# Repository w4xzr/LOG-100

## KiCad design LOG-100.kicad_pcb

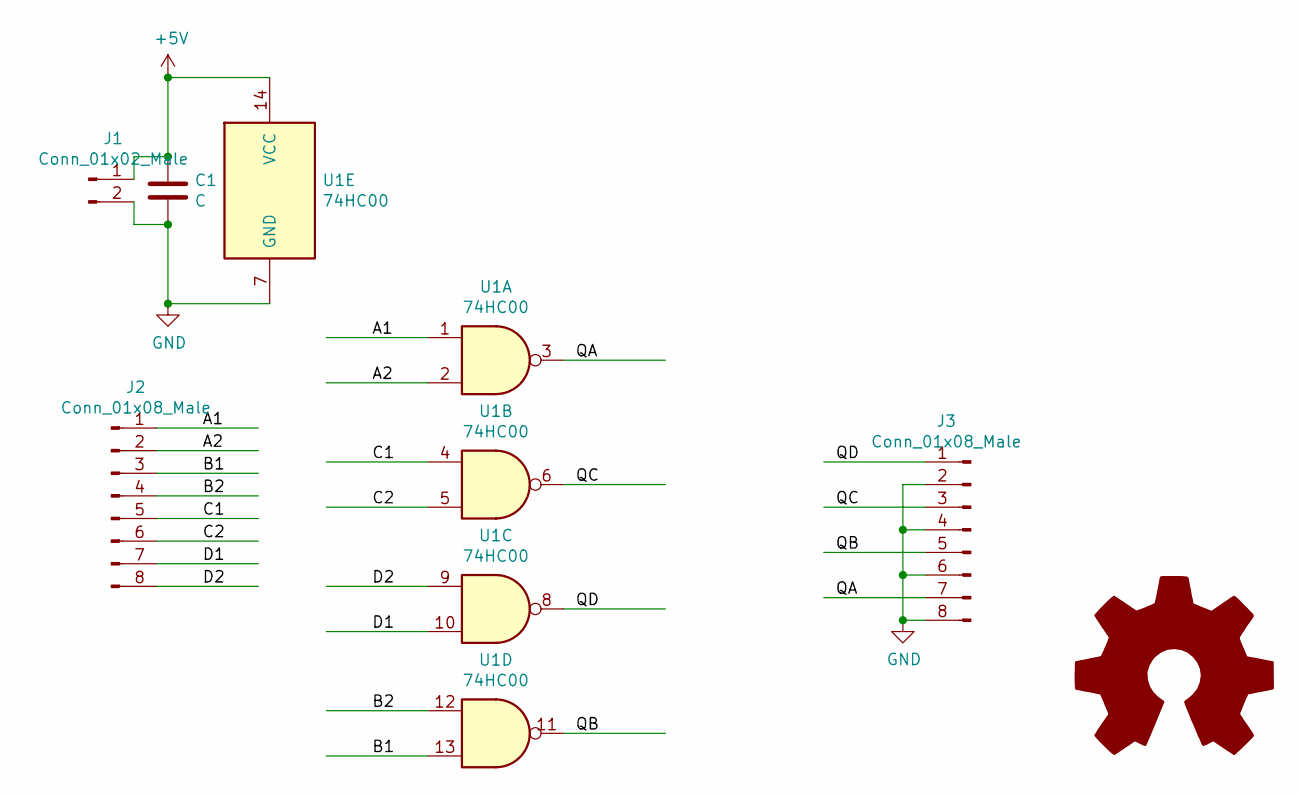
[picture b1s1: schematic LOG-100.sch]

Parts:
C1: C; C_Disc_D5.0mm_W2.5mm_P5.00mm
J1: Conn_01x02_Male; PinHeader_1x02_P2.54mm_Vertical
J2, J3: Conn_01x08_Male; PinHeader_1x08_P2.54mm_Vertical
U1: 74HC00; DIP-14_W7.62mm

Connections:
+5V: C1.1, J1.1, U1.14 (VCC)
/A1: J2.1, U1.1
/A2: J2.2, U1.2
/B1: J2.3, U1.13
/B2: J2.4, U1.12
/C1: J2.5, U1.4
/C2: J2.6, U1.5
/D1: J2.7, U1.10
/D2: J2.8, U1.9
/QA: J3.7, U1.3
/QB: J3.5, U1.11
/QC: J3.3, U1.6
/QD: J3.1, U1.8
GND: C1.2, J1.2, J3.2, J3.4, J3.6, J3.8, U1.7 (GND)

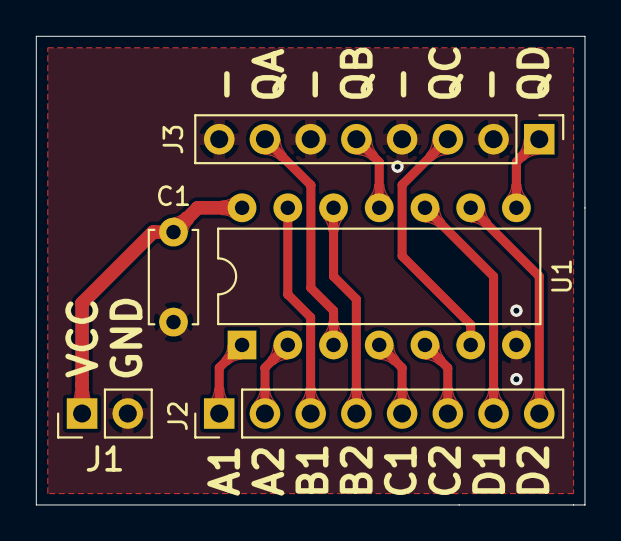
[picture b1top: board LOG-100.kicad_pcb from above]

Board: 2 copper layers, 30.5 x 26.0 mm, 5 parts (0 on the bottom side), 14 nets.

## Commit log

2020-07-03 init
2020-07-03 Updated Images: Fri Jul 3 23:35:11 UTC 2020 (Build 2)
    [skip ci]
2020-07-03 [ImgBot] Optimize images
    *Total -- 467.65kb -> 324.67kb (30.58%)
    /Images/Front.png -- 261.31kb -> 179.27kb (31.4%)
    /Images/Back.png -- 206.34kb -> 145.40kb (29.54%)
2020-07-03 Added README.md
2020-07-03 Updated Images: Fri Jul 3 23:59:20 UTC 2020 (Build 7)
    [skip ci]
2020-07-04 Cleanup
2020-07-04 Updated Images: Sat Jul 4 00:31:02 UTC 2020 (Build 12)
    [skip ci]
2020-07-04 Updated Images: Sat Jul 4 01:46:49 UTC 2020 (Build 18)
    [skip ci]
2020-07-04 Updated Images: Sat Jul 4 02:11:11 UTC 2020 (Build 23)
    [skip ci]
